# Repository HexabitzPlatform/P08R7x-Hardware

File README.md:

# P08R7x-Hardware
Hexabitz VL53L1 Time-of-Flight IR Sensor Module Hardware Design

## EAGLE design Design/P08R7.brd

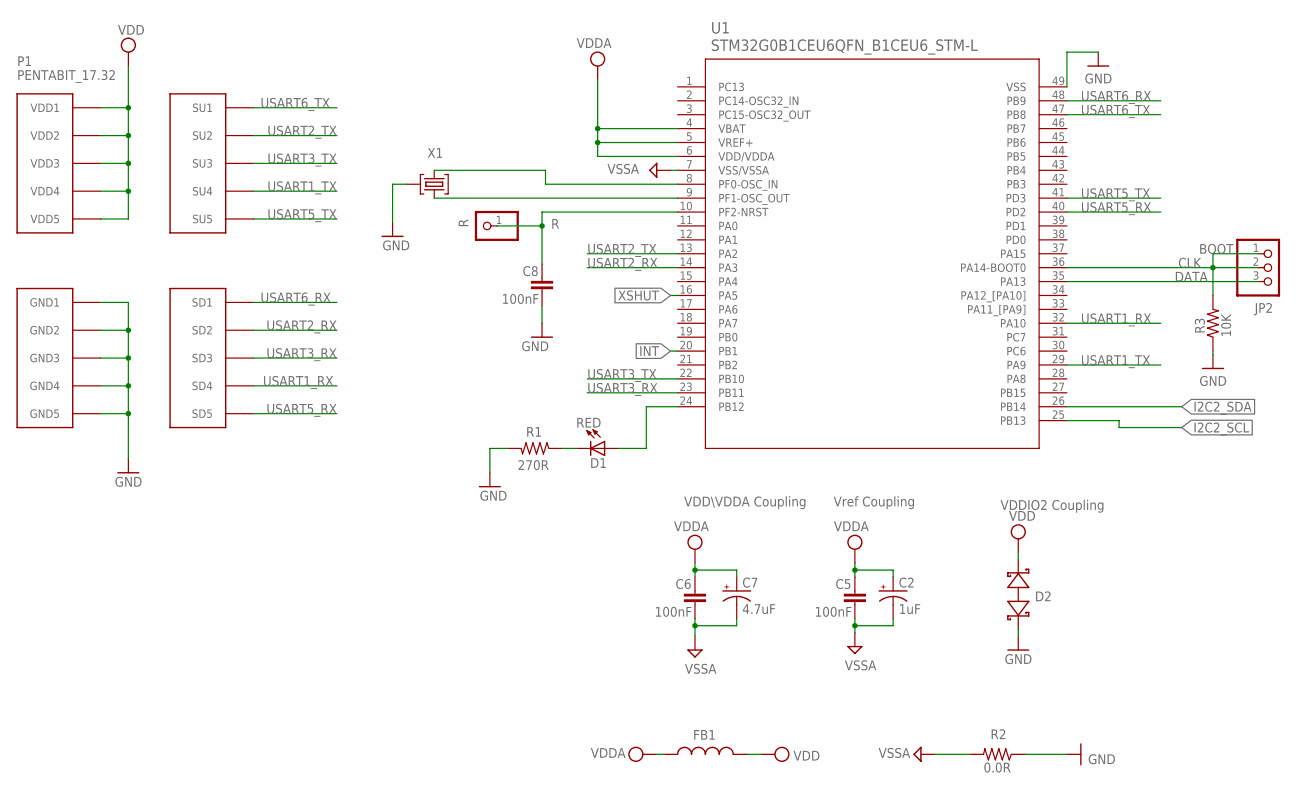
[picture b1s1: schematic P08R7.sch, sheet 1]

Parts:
C2: 1uF; C-0805-POL
C5, C6, C8: 100nF; C-0603
C7: 4.7uF; C-0805-POL
D1: RED; VLMS1300-GS08; MPN VLMS1300-GS08
D2: BOURNS_CDSOD323-T03SCBOURNS_CDSOD323-T03SC_0_0; BOURNS_CDSOD323-T03SC_0
FB1: FB-TDK_MMZ1608Y300B; MPN MMZ1608Y300B
JP2: PINHD-1X3; 1X03
P1: PENTABIT_17.32
R: R; 1X01
R1: 270R; R-0603
R2: 0.0R; R-0603; MPN RC0603JR-070RL
R3: 10K; R-0603
TRIMBLE-LOGO1: HEXA-LOGO
U1: STM32G0B1CEU6QFN_B1CEU6_STM-L; QFN_B1CEU6_STM-L
X1: XTALL_CSTCE8M00G52

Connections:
CLK: JP2.1, JP2.2, R3.2, U1.36 (PA14-BOOT0)
DATA: JP2.3, U1.35 (PA13)
GND: C8.2, D2.1 (A), P1.PAD_PD6 (GND1), P1.PAD_PD7 (GND2), P1.PAD_PD8 (GND3), P1.PAD_PD9 (GND4), P1.PAD_PD10 (GND5), R1.2, R2.1, R3.1, U1.49 (VSS), X1.P$2 (2); also elsewhere on the board
I2C2_SCL: U1.25 (PB13); also elsewhere on the board
I2C2_SDA: U1.26 (PB14); also elsewhere on the board
INT: U1.20 (PB1); also elsewhere on the board
unnamed: D1.C, R1.1
unnamed: D1.A, U1.24 (PB12)
unnamed: C8.1, R.1, U1.10 (PF2-NRST)
unnamed: U1.9 (PF1-OSC_OUT), X1.P$1 (1)
unnamed: U1.8 (PF0-OSC_IN), X1.P$3 (3)
USART1_RX: P1.PAD_PD4 (SD4), U1.32 (PA10)
USART1_TX: P1.PAD_PU4 (SU4), U1.29 (PA9)
USART2_RX: P1.PAD_PD2 (SD2), U1.14 (PA3)
USART2_TX: P1.PAD_PU2 (SU2), U1.13 (PA2)
USART3_RX: P1.PAD_PD3 (SD3), U1.23 (PB11)
USART3_TX: P1.PAD_PU3 (SU3), U1.22 (PB10)
USART5_RX: P1.PAD_PD5 (SD5), U1.40 (PD2)
USART5_TX: P1.PAD_PU5 (SU5), U1.41 (PD3)
USART6_RX: P1.PAD_PD1 (SD1), U1.48 (PB9)
USART6_TX: P1.PAD_PU1 (SU1), U1.47 (PB8)
VDD: D2.2 (C), FB1.2, P1.PAD_PU6 (VDD1), P1.PAD_PU7 (VDD2), P1.PAD_PU8 (VDD3), P1.PAD_PU9 (VDD4), P1.PAD_PU10 (VDD5); also elsewhere on the board
VDDA: C2.1 (+), C5.1, C6.1, C7.1 (+), FB1.1, U1.4 (VBAT), U1.5 (VREF+), U1.6 (VDD/VDDA)
VSSA: C2.2 (-), C5.2, C6.2, C7.2 (-), R2.2, U1.7 (VSS/VSSA)
XSHUT: U1.16 (PA5); also elsewhere on the board

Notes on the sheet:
Vref Coupling
VDDIO2 Coupling
VDD\VDDA Coupling
BOOT

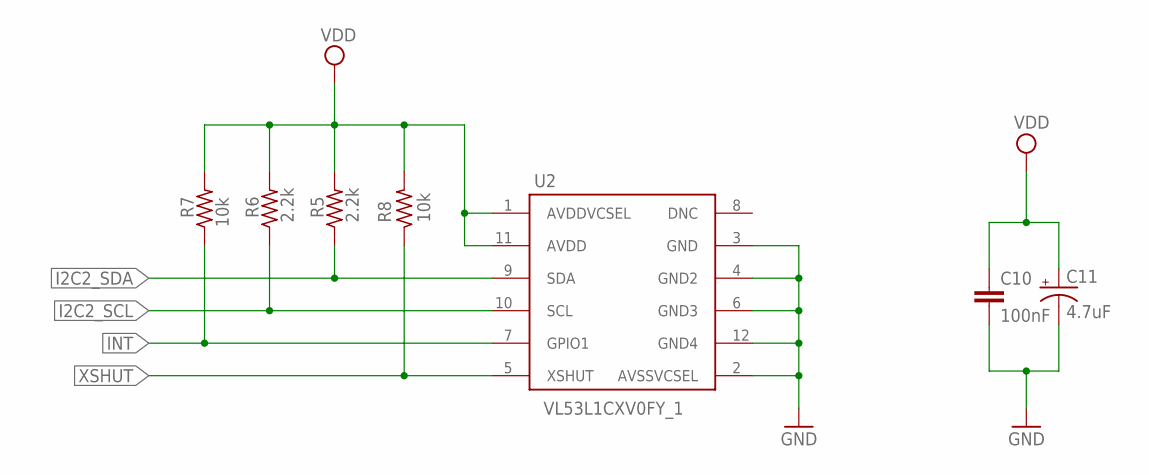
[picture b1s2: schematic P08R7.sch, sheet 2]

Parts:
C10: 100nF; C-0603
C11: 4.7uF; C-0805-POL
R5, R6: 2.2k; R-0603
R7, R8: 10k; R-0603
U2: VL53L1CXV0FY_1; VL53L1CXV0FY1

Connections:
GND: C10.2, C11.2 (-), U2.2 (AVSSVCSEL), U2.3 (GND), U2.4 (GND2), U2.6 (GND3), U2.12 (GND4); also elsewhere on the board
I2C2_SCL: R6.1, U2.10 (SCL); also elsewhere on the board
I2C2_SDA: R5.1, U2.9 (SDA); also elsewhere on the board
INT: R7.1, U2.7 (GPIO1); also elsewhere on the board
VDD: C10.1, C11.1 (+), R5.2, R6.2, R7.2, R8.2, U2.1 (AVDDVCSEL), U2.11 (AVDD); also elsewhere on the board
XSHUT: R8.1, U2.5 (XSHUT); also elsewhere on the board

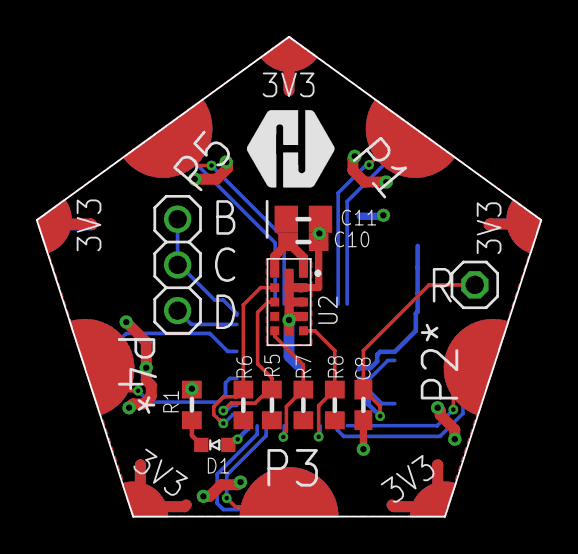
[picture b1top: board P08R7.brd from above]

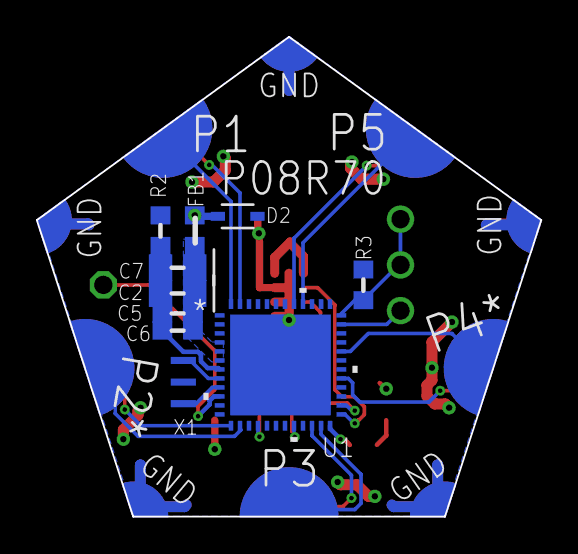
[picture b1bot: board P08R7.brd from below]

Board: 2 copper layers, 28.0 x 26.6 mm, 24 parts (10 on the bottom side), 25 nets.

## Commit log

2024-04-01 -Unreviewd Version
2024-04-01 -All Finish, Reviewed Version
2024-07-10 -Add TVS diode -Change the MCU to STM32G0B1CEU6 -Activate the thermal option for the polygon

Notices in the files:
parts and their libraries:
COPYRIGHT: Copyright (C) 2021 Ultra Librarian. All rights reserved.
